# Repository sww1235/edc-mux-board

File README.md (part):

# EDC-MUX-Board

This is part of the [EDC harness
project](https://github.com/sww1235/edc-harness) and provides, audio and PTT
routing and control routing.

This branch uses an FPGA to do digital audio mixing and muxing as well as signal
routing.

Due to using a FPGA, the functionality of the
[mixer](https://github.com/sww1235/portable-line-mixer) is also incorperated.

The initial plan is to use VHDL as the language of choice and then choose a FPGA
based on the actual requirements of the project.

All code, schematics and pcb layouts in this repo are released under MIT, unless
they are licensed under another license, in which case they are under that
license. If you are the maintainer of code that I have used in this project and
consider my license to be incompatible with your license, create an issue and we
can discuss it. This is a personal project with no hope or intention of ever
commercializing it.

## Overview of FPGA logic

All digital audio is using the I2S interface with PCM audio. Need a serial to
parallel converter to take serial data and turn it into parallel data that can
be fed into the parallel multipliers etc.

probably use existing off the shelf i2s to parallel vhdl blocks from
<https://opencore.com> with some modifications. Use 18 bit internal
busses.

Current plan is to use i2s to parallel converter from
[here](https://opencores.org/project/i2s_to_parallel) and modify it for i2s
output.

Use 16 bit audio with 18 bit adders/multipliers.

Digital volume control is done via 18x18 bit multipliers outputing to a double
width bus. IE
`S32 out_PCM = ((S18 ch1_PCM * S18 ch1_gain) + (S18 ch2_PCM * S18 ch2_gain) ... )`
where all S18 are only holding 16 bit signed values but shifted so MSB is at B17 rather than B15.

## Design Notes

Use ATSAMD21J18A microprocessor (ARM Cortex M0+), with separate ethernet mac+phy
chip (probably Wiznet W5500).

Use  TLV320AIC3206 from TI for the headset connections. (Integrated stereo
headphone amplifier along with ADC for mic).

Use MAX4910 4PDT beyond the rail switch to switch between headphone and line out
on the CODEC. Use

Use Master clock with clock buffers to provide MCLK for CODECs, and FPGA.
Additionally, use to clock microprocessor. Might have to use multi output clock
generator to run both wiznet chip and others off one generator.

Best plan is to run all IO at 3.3V LVCMOS standard including clocks.

2x 1:8 LVCMOS fan out clock buffer for 16 CODECs: CDCLVC1108 from TI.

CDCE706 clock generator with 6 independant outputs.

P82B96 bidirectional i2c bus buffer and voltage converter, used for interfacing
to device interface boards.

Use SiTIME MEMS Oscillator SiT1602BI-71-33E-48.000000, connect to RefP input on
clock generator

Use TS12A4514 NO SPST switches for PTT signalling on Interface boards.
Alternatively, if large numbers of switches are needed use a direct i2c
controlled XPST switch rather than using multiple chips.

## SAMD21 IO multiplexed function reference

| Pin | IO Pin | Multiplexed Peripheral function | Connected signal |
|-----|--------|---------------------------------|------------------|
| 10  | PB07   | N/A                             | RESETI2C         |
| 11  | PB08   |          |               |
| 12  | PB09   |          |               |
| 17  | PA08   | SERCOM0/PAD\[0\]                | MOSI             |
| 18  | PA09   | SERCOM0/PAD\[1\]                | \~SS             |
| 19  | PA10   | SERCOM0/PAD\[2\]                | MISO             |
| 20  | PA11   | SERCOM0/PAD\[3\]                | SCK              |
| 23  | PB10   | EXTINT\[10\]                    | CRC_ERROR        |
| 24  | PB11   | EXTINT\[11\]                    | CONF_DONE        |
| 25  | PB12   | SERCOM4/PAD\[0\]  (SDA)         | SDA              |
| 26  | PB13   | SERCOM4/PAD\[1\]  (SCL)         | SCL              |
| 29  | PA12   | EXTINT\[12\]                    | DEV_INT0         |
| 30  | PA13   | EXTINT\[13\]                    | DEV_INT1         |
| 31  | PA14   | XIN (external clock in)         | CLK3_MCU         |
| 32  | PA15   | EXTINT\[15\]                    | DEV_INT2         |
| 35  | PA16   | EXTINT\[0\]                     | DEV_INT3         |
| 36  | PA17   | EXTINT\[1\]                     | DEV_INT4         |
| 37  | PA18   | EXTINT\[2\]                     | DEV_INT5         |
| 38  | PA19   | EXTINT\[3\]                     | DEV_INT6         |
| 41  | PA20   | EXTINT\[4\]                     | DEV_INT7         |
| 42  | PA21   | EXTINT\[5\]                     | ATTACH_INT       |
| 43  | PA22   | EXTINT\[6\]                     | INIT_DONE        |
| 44  | PA23   | EXTINT\[7\]                     | \~STATUS         |
| 45  | PA24   | USB/DM                          | USB_D-           |
| 46  | PA25   | USB/DP                          | USB_D+           |
| 57  | PA30   | SWCLK                           | SWCLK            |
| 58  | PA31   | SWDIO                           | SWDIO            |

Available interrupts on:

Pin 11 / Pin 53 - EXTINT\[8\]
Pin 12 - EXTINT\[9\]
Pin 27 / Pin 59 - EXTINT\[14\]

## Device Interface Notes

Almost all devices are going to have to have an interface board to connect
between the 12 pin connector, and whatever IO is on the actual device.

The original hope was to only have passive components there, but this is looking
to be less practical now, especially since ptt signalling takes up 2 pins, and
is only needed on a very small percentage of devices. Additionally some radios
etc, need multiple ptt switch contacts.

New plan is to have semi-custom **As Small As Possible** interface boards for
devices. These might also simplify providing power to and from the devices
through the power distribution box.

Standardize the interface between mux board and interface. See
**Interface Specs** below for details.

Two different overall types of device: Headset and Device.

The Headset type includes headphones or earbuds that will be connected to the HP
terminals on the TLV320AIC3206. The device type has line outputs. All line
inputs need to be level adjusted with an adjustable pad as seen below. Mics
should be biased as necessary on the interface board and not expect biasing from
the TLV320AIC3206.

In general, each interface board has an I2C IO expander and a I2C flash chip (On
Semi CAT24C16 in WLCSP4 package) containing a board type number, which is read
by the microprocessor in order to set up the appropriate control logic and
determine the appropriate audio levels for the Codec. There will also be a
P82B96 chip for I2C level conversion for "long" distance signalling.

The detection of connection and disconnection of interfaces, is done via an
External Interrupt on the MCU, and with the `ID_PIN` on the connector connected
to ground, so when the device is connected, the pin will flip from high to low,
and when disconnected, it will flip from low to high via an external pull up
resistor on the main board.

There will also be application specific hardware such as ptt signalling or
volume control interpretation for headsets.

### Radio Interface Board Example

ptt switch for each channel, audio passthrough and bias voltage blocking

Has separate power connection

### Smartphone interface

Provides media control of smartphone, audio passthrough and bias voltage blocking.

Media control may be provided via emulating a headset or through some form of USB control.

Note: Android devices use different pinout and resistors to apple devices. Much
more feasible to support Android than Apple.

## Interface specs

Connector pinout:
(directions relative to mux (input = connecting to input on codec))

| Pin | Signal      |
|:----|:------------|
| 1   | SCL_HV      |
| 2   | SDA_HV      |
| 3   | Audio GND   |
| 4   | R Audio OUT |
| 5   | L Audio OUT |
| 6   | L Audio IN  |
| 7   | R Audio IN  |
| 8   | I2C_INT     |
| 9   | ID_PIN      |
| 10  | GND         |
| 11  | GND         |
| 12  | +12V        |

All analog audio IO is done at consumer line level. (IO direction is referenced
to MUX)

Consumer line level uses dBV as its reference. To convert between dBV and
voltage use following formulae:

```math
dBV => 20 * log(Vx/Vref)

0 dBV=Vref=1V

Vx is input voltage (RMS)
```

TLV320AIC3206 will accept signals with max value of 0.5VRMS. Probably need a pad
circuit like below to reduce voltage levels for line inputs. This pad circuit
will be implemented on an external interface board if needed. For general
consumer line level inputs, provide a adjustable resistor to tune VRMS so as to
not overdo attenuation if not needed.

(Device Output) Resistor divider with ~40dB attenuation. Attenuation in dB = 20*
log10((R1 + R2)/R2).

```
Input: o-----^v^v^v--o---o Output
               R1    |
                     >
                 R2  <
                     >
                     >
                     |
                 GND V
```

## I2C commands

Potentially generate interrupt on any physical input change to trigger a read
from i2c master. Will need to set data in `data_to_master` register then set
read_req high. (depends on how fast arduino can respond to interrupt)

Always have master send three bytes. Some instructions will ignore third byte.

### Command Explanations

#### Matrix Mixer:

All outputs receive all inputs. First want to select which output, then select
the volume register associated with that output and the selected input. Then
finally set the actual volume level.

<table>

<tr>

<th>Primary Bit Pattern (Command)</th>
<th>Secondary Bit Pattern (selection/data)</th>
<th>Tertiary bit pattern (data)</th>
<th>Description</th>

</tr>

<tr>

<td> <code>000X.XXXX</code> </td>

<td> <code>000Y.YYYY</code> </td>

<td> <code>VVVV.VVVV</code> </td>

<td> Matrix mixer controls. </br>Channels are represented with i2s channel 0
(left) using even numbers (starting from 0) and i2s channel 1 (right) using odd
numbers, so device 0 channel 0 is <code>00000</code> while device 1 channel 1 is
<code>00011</code>. The inputs and outputs are treated as 32 mono channels each
and left and right are only important in the control software. </br> Primary
selects output with bits 0-4.</br> Secondary selects which input volume is being
controlled with bits 0-4. </br> Tertiary is a 8 bit representation of the linear
volume control of the input in the output. Value from 0 to 255.
</br>So to zero the volume of input 4 channel 1 in output 8 channel 2,
you would send 3 i2c messages: <code>0001.1000</code> => <code>0000.0100</code>
=> <code>0000.0000</code></td>

</tr>

<tr>

<td> <code>01XX.XXXX</code> </td>

<td>  </td>

<td> </td>

<td>Reserved</td>

</tr>

<tr>

<td> <code>10XX.XXXX</code> </td>

<td>  </td>

<td> </td>

<td>Reserved</td>

</tr>

<tr>

<td> <code>1100.000X</code> </td>

<td> </td>

<td> </td>

<td>Reserved</td>

</tr>

</table>

## General Notes

Audio in PCM format is sampled at the sampling rate (normally 44.1kHz(CD) or
48kHz(DVD)) using 16-24 bits of resolution. Meaning each sample is represented
by a 16 to 24 bit number.

Therefor reading i2s data is clock in 16 bits of data into the left register,
then clock in 16 bits of data into the right register and repeat.

I2S by spec represents data in 2s complement format. In any bit width
conversion, truncation or zero fill is applied. Quoting from the I2S spec:

>When the system word length is greater than the transmitter word
>length, the word is truncated (least significant data bits are set to ‘0’)
>for data transmission. If the receiver is sent more bits than its word
>length, the bits after the LSB are ignored. On the other hand, if the
>receiver is sent fewer bits than its word length, the missing bits are
>set to zero internally. And so, the MSB has a fixed position, whereas
>the position of the LSB depends on the word length. The transmitter
>always sends the MSB of the next word one clock period after the
>WS changes.

## Extra parts

-   767KS1(X) 0.084 \[2.1\] id/od sealed locking power plug switchcraft
-   PCL722AS 0.08 \[2.0\] id/od sealed locking power jack switchcraft (these
    sizes are compatible with high amperage version
-   JCAP  power jack cover
-   35FM3AULS - Sealed locking 3.5mm panel mount jack switchcraft
-   35HDLBAU(S) 3.5mm sealed locking plug switchcraft (S=0.175 diameter cable, no S=0.29 diameter cable)

## TODO

-   CODE
-   Case
    -   Change lid screws to M2.5
    -   Move Oring inside screw line (use same as on portable line mixer)
    -   weight reduction on chassis and lid. Shrink wall thickness to 0.125",
        leave ribs on base for stiffness
    -   leave sealing flange and ribs on lid
    -   leave connector sides full thickness

## Power Consumption (Worst Case Assumptions)

| Device (Current Drawn) | +12V | +3V3  | +1V8  | +2V5   | +1V2  |
|:-----------------------|------|-------|-------|--------|-------|
| FPGA                   | 0A   | 20mA  | 0A    | 40mA   | 400mA |
| CODEC x16              | 0A   | 10mA  | 40mA  | 0A     | 0A    |
| P82B96 x16             | 2mA  | 0A    | 0A    | 0A     | 0A    |
| MAX4910 x16            | 0A   | 5uA   | 0A    | 0A     | 0A    |
| TCA9555                | 0A   | 2mA   | 0A    | 0A     | 0A    |
| TCA9548A x2            | 0A   | 35uA  | 0A    | 0A     | 0A    |
| CDCLVC1108 x2          | 0A   | 10mA  | 0A    | 0A     | 0A    |
| W5500                  | 0A   | 132mA | 0A    | 0A     | 0A    |
| SAMD21 MCU             | 0A   | 25mA  | 0A    | 0A     | 0A    |
|                        |      |       |       |        |       |
| Totals                 | 32mA | 360mA | 640mA | 40mA   | 400mA |
| Total @ 3V3 (+20%)     | 0A   | 360mA | 419mA | 36.4mA | 175mA |
| Total @ 12V (+20%)     | 32mA | 327mA | 0A    | 0A     | 0A    |
| Total 12V required     | 360mA | @12V~=4.32W  |
### CODEC Summary

From Application Guide:

Stereo ADC power consumption w/ DVDD == AVDD == 1V8, 48kHz:

Highest Performance Config (max listed) = 18.2mW
Normal (max listed) = 11.5mW

Stereo DAC power consumption w/ DVDD == AVDD == 1V8, 48kHz:

Headphone out (32Ω) (max listed) = 10.9mW

Line out (max listed) = 9.2mW

Worst case assumption of DAC + ADC = 30mA

Assume +10mA for core, +10mA for IO

### SAMD MCU Summary

Static Power draw 4.5mA (worst case)

\+ SERCOM.I2CM 70uA (worst case estimate)

\+ SERCOM.SPI 70uA (worst case estimate)

\+ ADC x16 1.25mA (absolute worst case, since sampling rate is far lower than datasheet numbers)

Total = 24.64mA ~=25mA

## Acknowledgements

I2S to parallel VHDL from
[opencores](https://opencores.org/project/i2s_to_parallel) released under GPL

I2C slave VHDL in submodule from
[here](https://github.com/sww1235/FPGA-I2C-Slave) which was [forked from
here](https://github.com/oetr/FPGA-I2C-Slave) released under MIT.

## References

-   <http://www.epanorama.net/circuits/line_to_mic.html>
-   <http://www.n1gy.com/headset-adaptor.html>
-   <http://www.mobilinkd.com/category/hacking/>
-   <http://ham.stackexchange.com/questions/5244/2-pin-kenwood-to-sound-card-beofeng-uv-82hp-asus-xonar-essence-stx>
-   <http://uuki.kapsi.fi/dl/uv5r_spkmic.pdf>
-   <http://www.n1gy.com/headset-adaptor-for-kenwood--baofeng-and-wouxun-hts.html>
-   <http://electronics.stackexchange.com/questions/71335/how-to-amplify-electret-microphone-to-range-from-0-5v-with-bias-of-2-5v>
-   <https://www.invensense.com/wp-content/uploads/2015/02/Using-a-MEMS-Microphone-in-a-2-Wire-Microphone-Circuit.pdf>
-   <http://www.brenorbrophy.com/HG/head_set_ptt.htm>
-   <http://electronics.stackexchange.com/questions/25229/do-electret-condenser-microphones-require-phantom-power>
-   <http://electronics.stackexchange.com/questions/27452/coupling-electret-microphone-input-to-linear-audio-output?rq=1>
-   <http://electronics.stackexchange.com/questions/261258/electret-microphone-how-does-it-work?rq=1>
-   <https://forums.radioreference.com/radio-direction-finding-forum/297920-baofeng-foxhunt-transmitter.html>
-   <https://www.reddit.com/r/amateurradio/comments/2jd4wr/line_level_to_high_impedance_input/>
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
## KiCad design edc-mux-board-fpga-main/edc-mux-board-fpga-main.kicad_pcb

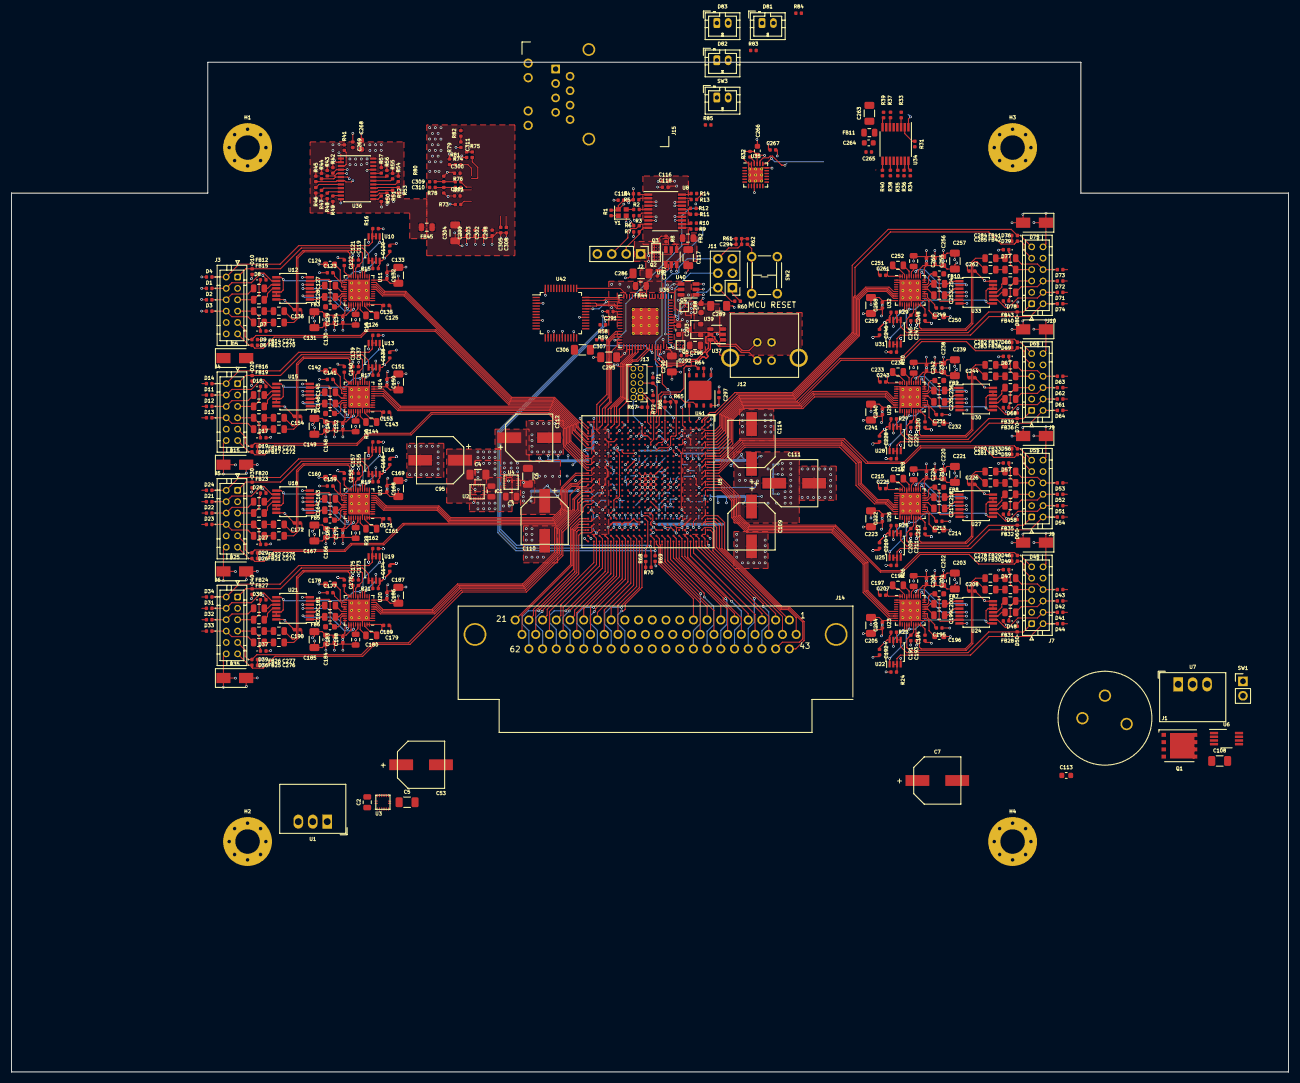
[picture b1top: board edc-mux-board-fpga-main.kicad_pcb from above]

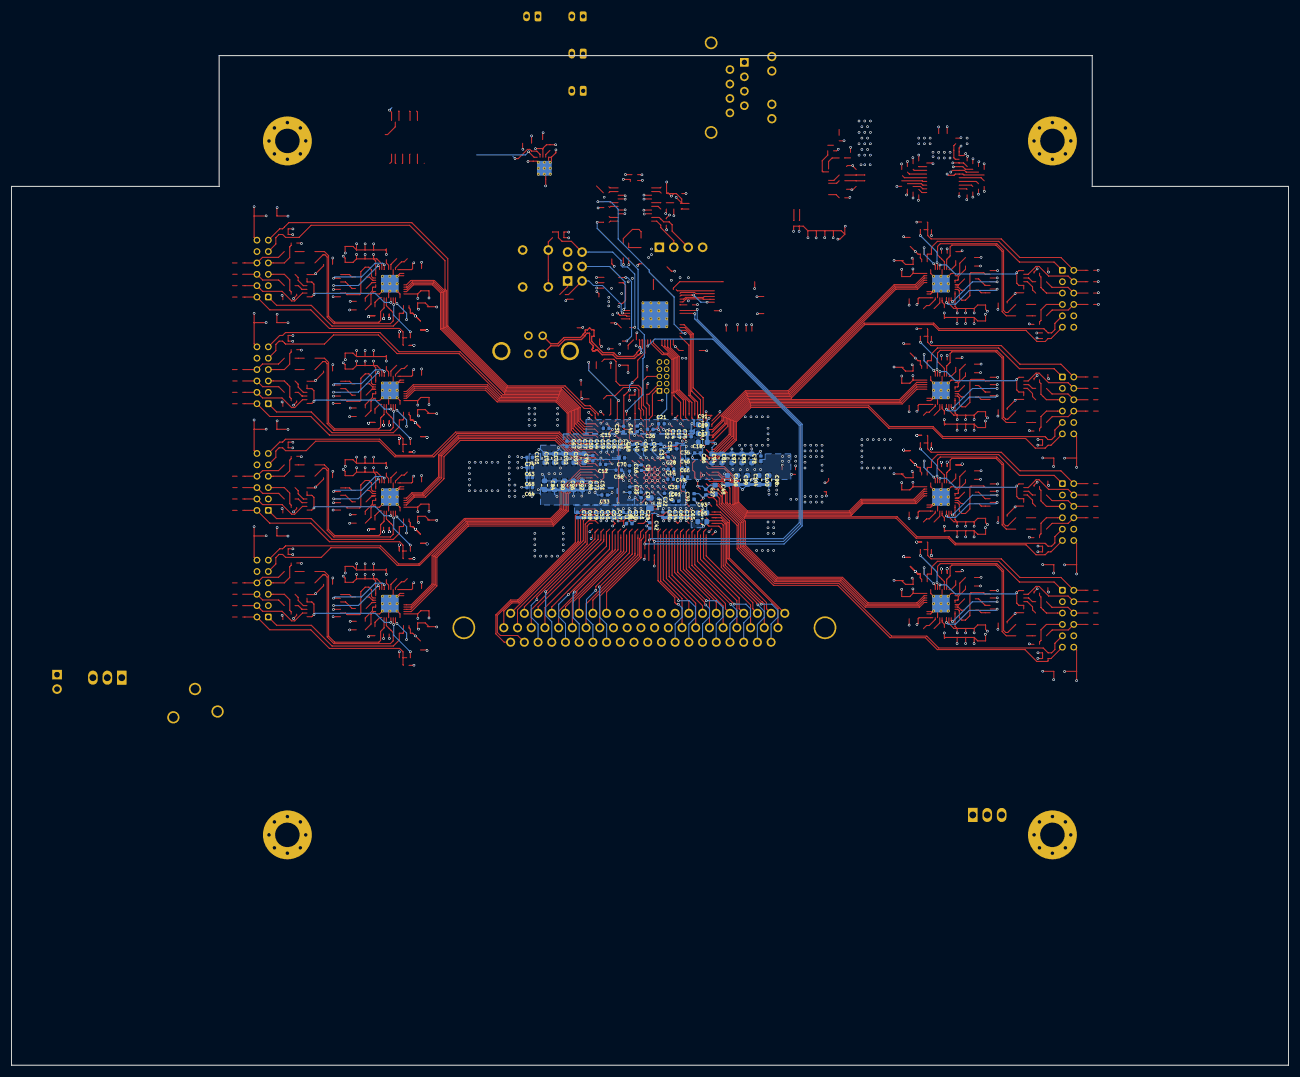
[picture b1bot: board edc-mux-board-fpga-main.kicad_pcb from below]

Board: 4 copper layers, 224.5 x 177.5 mm, 593 parts (99 on the bottom side), 460 nets.

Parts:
C1, C2, C3: 4.7uF X7R; C_0805_2012Metric
C4, C5, C6, C108, C117, C131, C133, C149, C151, C167, C169, C185, C187, C203, C205, C221, C223, C239, C241, C257, C259, C263, C286, C289, C290, C295, C304, C306: 10uF X7R; C_1206_3216Metric
C7, C53, C95, C109, C110, C111, C112, C114: 47uF; CP_ELEC_8.3x8.3x11.7mm_SMD
C8, C9, C10, C11, C12, C13, C14, C15, C16, C17, C18, C19, C20, C21, C22, C23, C24, C25, C26, C28, C29, C31, C32, C34, C37, C305: 4.7nF X7R; C_0402_1005Metric
C27, C30, C33, C36, C39, C41, C44, C47, C50, C52, C55, C57, C59, C60, C62, C308: 10nF X7R; C_0402_1005Metric
C35, C38, C40, C43, C46, C49, C51, C54, C56, C58: 47nF X7R; C_0402_1005Metric
C42, C45, C61, C63, C64, C65, C66, C67, C68, C69, C70, C71, C72, C73, C74, C75, C76, C77, C78, C79, C80, C82, C115, C116, C118, C120, C122, C123, C129, C132, C134, C135, C136, C138, C140, C141, C147, C150, C152, C153, C154, C156, C158, C159, C165, C168, C170, C171, C172, C174, C176, C177, C183, C186, C188, C189, C190, C192, C194, C195, C201, C204, C206, C207, C208, C210, C212, C213, C219, C222, C224, C225, C226, C228, C230, C231, C237, C240, C242, C243, C244, C246, C248, C249, C255, C258, C260, C261, C262, C265, C267, C269, C287, C291, C292, C297, C298, C299, C300, C301, C302, C303, C307: 100nF X7R; C_0402_1005Metric
C48, C85, C87, C89, C91, C93, C98, C99, C100, C101, C102, C103, C104, C105, C106, C107, C124, C130, C142, C148, C160, C166, C178, C184, C196, C202, C214, C220, C232, C238, C250, C256, C264, C266, C268, C288, C293: 1uF X7R; C_0603_1608Metric
C81, C83, C84, C86, C88, C90, C92, C94, C96, C97, C113: 220nF X7R; C_0603_1608Metric
C119, C121, C137, C139, C155, C157, C173, C175, C191, C193, C209, C211, C227, C229, C245, C247: 33pF NP0; C_0402_1005Metric
C125, C126, C143, C144, C161, C162, C179, C180, C197, C198, C215, C216, C233, C234, C251, C252, C296: 2.2uF X7R; C_0805_2012Metric
C127, C128, C145, C146, C163, C164, C181, C182, C199, C200, C217, C218, C235, C236, C253, C254, C270, C271, C272, C273, C274, C275, C276, C277, C278, C279, C280, C281, C282, C283, C284, C285: 1uF X7R flex; C_0805_2012Metric
C294: 100pF C0G; C_0402_1005Metric
C309, C310: 6.8nF X7R; C_0402_1005Metric
C311: 22nF X7R; C_0402_1005Metric
D1, D2, D3, D4, D6, D7, D8, D9, D10, D11, D12, D13, D14, D16, D17, D18, D19, D20, D21, D22, D23, D24, D26, D27, D28, D29, D30, D31, D32, D33, D34, D36, D37, D38, D39, D40, D41, D42, D43, D44, D46, D47, D48, D49, D50, D51, D52, D53, D54, D56, D57, D58, D59, D60, D61, D62, D63, D64, D66, D67, D68, D69, D70, D71, D72, D73, D74, D76, D77, D78, D79, D80: 30pF 30kV; D_0402_1005Metric
D5, D15, D25, D35, D45, D55, D65, D75: 12V_Vrso; D_SMA
D81: LINK_GRN; JST_PH_B2B-PH-K_1x02_P2.00mm_Vertical
D82: ACT_YLW; JST_PH_B2B-PH-K_1x02_P2.00mm_Vertical
D83: PWR_RED; JST_PH_B2B-PH-K_1x02_P2.00mm_Vertical
FB1, FB2, FB11, FB12, FB13, FB14, FB15, FB16, FB17, FB18, FB19, FB20, FB21, FB22, FB23, FB24, FB25, FB26, FB27, FB28, FB29, FB30, FB31, FB32, FB33, FB34, FB35, FB36, FB37, FB38, FB39, FB40, FB41, FB42, FB43, FB44, FB45: 600Ω @ 100MHz; L_0805_2012Metric
FB3, FB4, FB5, FB6, FB7, FB8, FB9, FB10: 220Ω/2A; L_0603_1608Metric
H1, H2, H3, H4: MountingHole_Pad; MountingHole_4.3mm_M4_Pad_Via
J1: Power In; PCL712AS
J2: OSC_PRG_HDR; PinHeader_1x04_P2.54mm_Vertical
J3, J4, J5, J6, J7, J8, J9, J10: Device; JST_PHD_B12B-PHDSS_2x06_P2.00mm_Vertical
J11: PRG/SWD; PinHeader_2x03_P2.54mm_Vertical
J12: USB PRG; UJ2-BV-1-TH
J13: FPGA_JTAG; PinHeader_2x05_P1.27mm_Vertical
J14: DC-62F; 09564525612
J15: RJ45_Magnetics_100BaseTX_No_LEDS; J1_Series_RJ45
Q1: CSD18501Q5A; TDSON-8-1
Q2, Q3, Q4, Q5: CSD22206W; DSBGA9
R1, R3, R4, R5, R60, R67: 1kΩ; R_0402_1005Metric
R2, R74, R75, R76, R77: 0Ω; R_0402_1005Metric
R6, R7, R31, R32, R41, R42, R43, R44, R45, R46, R47, R48, R49, R50, R51, R52, R53, R54, R55, R56, R57, R58, R59, R65, R66, R68, R69, R70, R71, R72: 10kΩ; R_0402_1005Metric
R8: 470kΩ; R_0402_1005Metric
R9, R10, R11, R12, R13, R14, R33, R34, R35, R36, R37, R38, R39, R40: 5Ω; R_0402_1005Metric
R15, R16, R17, R18, R19, R20, R21, R22, R23, R24, R25, R26, R27, R28, R29, R30: 750Ω; R_0402_1005Metric
R61: 2k2Ω; R_0402_1005Metric
R62, R83, R84, R85: 330Ω; R_0402_1005Metric
R64: 25Ω; R_0402_1005Metric
R73: 12.4Ω 1%; R_0402_1005Metric
R78, R80: 82Ω 1%; R_0402_1005Metric
R79, R81: 49.9Ω 1%; R_0402_1005Metric
R82: 10Ω 1%; R_0402_1005Metric
SW1: Power Switch; PinHeader_1x02_P2.54mm_Vertical
SW2: Reset (Microprocessor); TL1105
SW3: LED_EN; JST_PH_B2B-PH-K_1x02_P2.00mm_Vertical
U1: R-78B3.3-2.0; Converter_DCDC_RECOM_R-78B-2.0_THT
U2, U3: EP5358HUI; ENPIRION_QFN16_2.5x2.25x1.1mm-0.4mm
U4: EP5358LUI; ENPIRION_QFN16_2.5x2.25x1.1mm-0.4mm
U5: 10CL040YF484I7G; FBGA-484_23.0x23.0mm_Layout22x22_P1.0mm
U6: LM74610-Q1; VSSOP-8_3.0x3.0mm_P0.65mm
U7: R-78B12-2.0; Converter_DCDC_RECOM_R-78B-2.0_THT
U8: CDCE706; TSSOP-20_4.4x6.5mm_P0.65mm
U9, U40: LTC4412; TSOT-23-6
U10, U13, U16, U19, U22, U25, U28, U31: P82B96; TSSOP-8_3x3mm_P0.65mm
U11, U14, U17, U20, U23, U26, U29, U32: TLV320AIC3206; UQFN-40-1EP_5x5mm_P0.4mm_EP3.8x3.8mm_ThermalVias
U12, U15, U18, U21, U24, U27, U30, U33: FSA2367; TSSOP-14_4.4x5mm_P0.65mm
U34: CDCLVC1108; TSSOP-16_4.4x5mm_P0.65mm
U35: TCA9555RTWR; QFN-24-1EP_4x4mm_P0.5mm_EP2.6x2.6mm_ThermalVias
U36: TCA9548A; TSSOP-24_4.4x7.8mm_P0.65mm
U37: TPD3S014; SOT-23-6
U38: SAMD21JXXAM; QFN-64-1EP_9x9mm_P0.5mm_EP4.7x4.7mm_ThermalVias
U39: MCP1812; SOT-23
U41: S25FL128L; WSON-8-1EP_6x5mm_P1.27mm_EP3.4x4mm
U42: W5500; TQFP-48_7x7mm_P0.5mm
Y1: SiT1602BI-71-33E-48.000000; Crystal_SMD_2016-4Pin_2.0x1.6mm

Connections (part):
+1V2: C6.1, C8.1, C9.1, C10.1, C13.1, C16.1, C19.1, C22.1, C25.1, C28.1, C31.1, C35.1, C38.1, C40.1, C43.1, C46.1, C49.1, C51.1, C54.1, C56.1, C58.1, C61.1, C63.1, C64.1, C66.1, C68.1, C70.1, C72.1, C74.1, C76.1, C78.1, C81.1, C83.1, C84.1, C86.1, C88.1, C90.1, C92.1, C94.1, C96.1, C97.1, C98.1, C99.1, C100.1, C101.1, C102.1, C103.1, C104.1, C105.1, C106.1, C107.1, C109.1, C110.1, C111.1, C112.1, C114.1, FB1.1, U4.5, U4.7, U4.8, U5.G12, U5.H9, U5.J10, U5.J11, U5.J12, U5.J13, U5.J14, U5.J16, U5.K9, U5.K14, U5.K15, U5.L9, U5.L14, U5.L16, U5.M9, U5.M14, U5.M15, U5.N9, U5.N14, U5.P9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
+1V8: C5.1, C129.2, C130.2, C131.2, C134.2, C135.2, C147.2, C148.2, C149.2, C152.2, C153.2, C165.2, C166.2, C167.2, C170.2, C171.2, C183.2, C184.2, C185.2, C188.2, C189.2, C201.2, C202.2, C203.2, C206.2, C207.2, C219.2, C220.2, C221.2, C224.2, C225.2, C237.2, C238.2, C239.2, C242.2, C243.2, C255.2, C256.2, C257.2, C260.2, C261.2, U3.5, U3.7, U3.8, U11.29, U11.30, U11.32, U11.39, U11.40, U14.29, U14.30, U14.32, U14.39, U14.40, U17.29, U17.30, U17.32, U17.39, U17.40, U20.29, U20.30, U20.32, U20.39, U20.40, U23.29, U23.30, U23.32, U23.39, U23.40, U26.29, U26.30, U26.32, U26.39, U26.40, U29.29, U29.30, U29.32, U29.39, U29.40, U32.29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
+2V5: C4.1, C11.1, C14.1, C17.1, C20.1, C23.1, C26.1, C29.1, C32.1, C34.1, C37.1, C41.1, C44.1, C47.1, C50.1, C52.1, C55.1, C57.1, C59.1, C60.1, C62.1, C65.1, C67.1, C69.1, C71.1, C73.1, C75.1, C77.1, C79.1, C80.1, C82.1, C85.1, C87.1, C89.1, C91.1, C93.1, C95.1, J13.9, R71.2, R72.2, U2.5, U2.7, U2.8, U5.F18, U5.G6, U5.T6, U5.U18
+3V3: C1.1, C2.1, C3.1, C7.1, C12.1, C15.1, C18.1, C21.1, C24.1, C27.1, C30.1, C33.1, C36.1, C39.1, C42.1, C45.1, C48.1, C53.1, C132.2, C133.1, C136.2, C150.2, C151.1, C154.2, C168.2, C169.1, C172.2, C186.2, C187.1, C190.2, C204.2, C205.1, C208.2, C222.2, C223.1, C226.2, C240.2, C241.1, C244.2, C258.2, C259.1, C262.2, C263.1, C266.1, C267.2, C268.1, C269.2, C294.2, C297.2, C306.2, C307.2, FB11.2, FB45.2, J11.1, J13.8, Q2.C1, Q2.C2, Q2.C3, Q4.C1, Q4.C2, Q4.C3, R32.2, R41.2, R42.2, R43.2, R44.2, R45.2, R46.2, R47.2, R48.2, R49.2, R50.2, R51.2, R52.2, R53.2, R54.2, R55.2, R56.2, R57.2, R58.2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
+12V: C120.1, C138.1, C156.1, C174.1, C192.1, C210.1, C228.1, C246.1, D5.1, D15.1, D25.1, D35.1, D45.1, D55.1, D65.1, D75.1, J3.12, J4.12, J5.12, J6.12, J7.12, J8.12, J9.12, J10.12, J14.9, J14.12, J14.13, J14.30, J14.31, J14.34, R15.1, R16.1, R17.1, R18.1, R19.1, R20.1, R21.1, R22.1, R23.1, R24.1, R25.1, R26.1, R27.1, R28.1, R29.1, R30.1, U1.1, U7.3, U10.8, U13.8, U16.8, U19.8, U22.8, U25.8, U28.8, U31.8
/ATTACH_INT: U5.R1, U38.42
/Bottom Side Connector Interconnects/BCLK8: J14.15, U5.R22
/Bottom Side Connector Interconnects/BCLK9: J14.17, U5.V22
/Bottom Side Connector Interconnects/BCLK10: J14.19, U5.AA22
/Bottom Side Connector Interconnects/BCLK11: J14.21, U5.AB18
/Bottom Side Connector Interconnects/BCLK12: J14.2, U5.A20
/Bottom Side Connector Interconnects/BCLK13: J14.4, U5.D22
/Bottom Side Connector Interconnects/BCLK14: J14.6, U5.G22
/Bottom Side Connector Interconnects/BCLK15: J14.8, U5.K22
/Bottom Side Connector Interconnects/DIN8: J14.14, U5.P22
/Bottom Side Connector Interconnects/DIN9: J14.16, U5.U22
/Bottom Side Connector Interconnects/DIN10: J14.18, U5.Y22
/Bottom Side Connector Interconnects/DIN11: J14.20, U5.AB19
/Bottom Side Connector Interconnects/DIN12: J14.1, U5.A19
/Bottom Side Connector Interconnects/DIN13: J14.3, U5.C22
/Bottom Side Connector Interconnects/DIN14: J14.5, U5.F22
/Bottom Side Connector Interconnects/DIN15: J14.7, U5.J22
/Bottom Side Connector Interconnects/DOUT8: J14.35, U5.P21
/Bottom Side Connector Interconnects/DOUT9: J14.37, U5.U21
/Bottom Side Connector Interconnects/DOUT10: J14.39, U5.Y21
/Bottom Side Connector Interconnects/DOUT11: J14.41, U5.AA19
/Bottom Side Connector Interconnects/DOUT12: J14.22, U5.B19
/Bottom Side Connector Interconnects/DOUT13: J14.24, U5.C21
/Bottom Side Connector Interconnects/DOUT14: J14.26, U5.F21
/Bottom Side Connector Interconnects/DOUT15: J14.28, U5.J21
/Bottom Side Connector Interconnects/WCLK8: J14.36, U5.R21
/Bottom Side Connector Interconnects/WCLK9: J14.38, U5.V21
/Bottom Side Connector Interconnects/WCLK10: J14.40, U5.AA21
/Bottom Side Connector Interconnects/WCLK11: J14.42, U5.AA18
/Bottom Side Connector Interconnects/WCLK12: J14.23, U5.B20
/Bottom Side Connector Interconnects/WCLK13: J14.25, U5.D21
/Bottom Side Connector Interconnects/WCLK14: J14.27, U5.G21
/Bottom Side Connector Interconnects/WCLK15: J14.29, U5.K21
/Bottom Side Connector Interconnects/~RESET~I2C: J14.33, R41.1, U36.3, U38.10
/CODEC interconnection sheet/BCLK0: U5.AA4, U11.6
/CODEC interconnection sheet/BCLK1: U5.AA8, U14.6
/CODEC interconnection sheet/BCLK2: U5.AA11, U17.6
/CODEC interconnection sheet/BCLK3: U5.AA14, U20.6
/CODEC interconnection sheet/BCLK4: U5.B12, U23.6
/CODEC interconnection sheet/BCLK5: U5.B9, U26.6
/CODEC interconnection sheet/BCLK6: U5.B6, U29.6
/CODEC interconnection sheet/BCLK7: U5.B3, U32.6
/CODEC interconnection sheet/Clock and I2C distribution/CLK_DISTRO_3V3_1: C264.2, C265.1, FB11.1, R31.2, U34.5, U34.10, U34.14
/CODEC interconnection sheet/DIN0: U5.AA3, U11.8
/CODEC interconnection sheet/DIN1: U5.AA7, U14.8
/CODEC interconnection sheet/DIN2: U5.AA10, U17.8
/CODEC interconnection sheet/DIN3: U5.AA13, U20.8
/CODEC interconnection sheet/DIN4: U5.B13, U23.8
/CODEC interconnection sheet/DIN5: U5.B10, U26.8
/CODEC interconnection sheet/DIN6: U5.B7, U29.8
/CODEC interconnection sheet/DIN7: U5.B4, U32.8
/CODEC interconnection sheet/DOUT0: U5.AB3, U11.9
/CODEC interconnection sheet/DOUT1: U5.AB7, U14.9
/CODEC interconnection sheet/DOUT2: U5.AB10, U17.9
/CODEC interconnection sheet/DOUT3: U5.AB13, U20.9
/CODEC interconnection sheet/DOUT4: U5.A13, U23.9
/CODEC interconnection sheet/DOUT5: U5.A10, U26.9
/CODEC interconnection sheet/DOUT6: U5.A7, U29.9
/CODEC interconnection sheet/DOUT7: U5.A4, U32.9
/CODEC interconnection sheet/Interface - Connector 0/AUD_GND: D1.1, J3.4, U12.9
/CODEC interconnection sheet/Interface - Connector 0/GND_SENSE: FB3.1, U11.28, U12.6
/CODEC interconnection sheet/Interface - Connector 0/HPL: U11.31, U12.4
/CODEC interconnection sheet/Interface - Connector 0/HPR: U11.33, U12.2
/CODEC interconnection sheet/Interface - Connector 0/HP_~LINE~_SEL: U11.15, U12.8, U12.12, U12.13
/CODEC interconnection sheet/Interface - Connector 0/LINE_OUT_L: C127.1, U12.3
/CODEC interconnection sheet/Interface - Connector 0/LINE_OUT_R: C128.1, U12.1
/CODEC interconnection sheet/Interface - Connector 0/L_IN: C119.2, C271.1, U11.17
/CODEC interconnection sheet/Interface - Connector 0/L_OUT: FB12.2, U12.10
/CODEC interconnection sheet/Interface - Connector 0/REF: C124.2, U11.22
/CODEC interconnection sheet/Interface - Connector 0/R_IN: C121.2, C270.2, U11.18
/CODEC interconnection sheet/Interface - Connector 0/R_OUT: FB15.1, U12.11
/CODEC interconnection sheet/Interface - Connector 0/SCL_HV: D10.1, J3.1, R15.2, U10.5, U10.6
/CODEC interconnection sheet/Interface - Connector 0/SDA_HV: D4.1, J3.2, R16.2, U10.2, U10.3
/CODEC interconnection sheet/Interface - Connector 0/VNEG: C126.2, U11.35
/CODEC interconnection sheet/Interface - Connector 1/AUD_GND: D11.1, J4.4, U15.9
/CODEC interconnection sheet/Interface - Connector 1/GND_SENSE: FB4.1, U14.28, U15.6
/CODEC interconnection sheet/Interface - Connector 1/HPL: U14.31, U15.4
/CODEC interconnection sheet/Interface - Connector 1/HPR: U14.33, U15.2
/CODEC interconnection sheet/Interface - Connector 1/HP_~LINE~_SEL: U14.15, U15.8, U15.12, U15.13
/CODEC interconnection sheet/Interface - Connector 1/LINE_OUT_L: C145.1, U15.3
/CODEC interconnection sheet/Interface - Connector 1/LINE_OUT_R: C146.1, U15.1
/CODEC interconnection sheet/Interface - Connector 1/L_IN: C137.2, C273.1, U14.17
/CODEC interconnection sheet/Interface - Connector 1/L_OUT: FB16.2, U15.10
/CODEC interconnection sheet/Interface - Connector 1/REF: C142.2, U14.22
/CODEC interconnection sheet/Interface - Connector 1/R_IN: C139.2, C272.2, U14.18
/CODEC interconnection sheet/Interface - Connector 1/R_OUT: FB19.1, U15.11
/CODEC interconnection sheet/Interface - Connector 1/SCL_HV: D20.1, J4.1, R17.2, U13.5, U13.6
/CODEC interconnection sheet/Interface - Connector 1/SDA_HV: D14.1, J4.2, R18.2, U13.2, U13.3
/CODEC interconnection sheet/Interface - Connector 1/VNEG: C144.2, U14.35
/CODEC interconnection sheet/Interface - Connector 2/AUD_GND: D21.1, J5.4, U18.9
/CODEC interconnection sheet/Interface - Connector 2/GND_SENSE: FB5.1, U17.28, U18.6
/CODEC interconnection sheet/Interface - Connector 2/HPL: U17.31, U18.4
/CODEC interconnection sheet/Interface - Connector 2/HPR: U17.33, U18.2
/CODEC interconnection sheet/Interface - Connector 2/HP_~LINE~_SEL: U17.15, U18.8, U18.12, U18.13
/CODEC interconnection sheet/Interface - Connector 2/LINE_OUT_L: C163.1, U18.3
/CODEC interconnection sheet/Interface - Connector 2/LINE_OUT_R: C164.1, U18.1
/CODEC interconnection sheet/Interface - Connector 2/L_IN: C155.2, C275.1, U17.17
/CODEC interconnection sheet/Interface - Connector 2/L_OUT: FB20.2, U18.10
/CODEC interconnection sheet/Interface - Connector 2/REF: C160.2, U17.22
/CODEC interconnection sheet/Interface - Connector 2/R_IN: C157.2, C274.2, U17.18
/CODEC interconnection sheet/Interface - Connector 2/R_OUT: FB23.1, U18.11
/CODEC interconnection sheet/Interface - Connector 2/SCL_HV: D30.1, J5.1, R19.2, U16.5, U16.6
/CODEC interconnection sheet/Interface - Connector 2/SDA_HV: D24.1, J5.2, R20.2, U16.2, U16.3
/CODEC interconnection sheet/Interface - Connector 2/VNEG: C162.2, U17.35
/CODEC interconnection sheet/Interface - Connector 3/AUD_GND: D31.1, J6.4, U21.9
/CODEC interconnection sheet/Interface - Connector 3/GND_SENSE: FB6.1, U20.28, U21.6
/CODEC interconnection sheet/Interface - Connector 3/HPL: U20.31, U21.4
/CODEC interconnection sheet/Interface - Connector 3/HPR: U20.33, U21.2
/CODEC interconnection sheet/Interface - Connector 3/HP_~LINE~_SEL: U20.15, U21.8, U21.12, U21.13
/CODEC interconnection sheet/Interface - Connector 3/LINE_OUT_L: C181.1, U21.3
/CODEC interconnection sheet/Interface - Connector 3/LINE_OUT_R: C182.1, U21.1
/CODEC interconnection sheet/Interface - Connector 3/L_IN: C173.2, C277.1, U20.17
/CODEC interconnection sheet/Interface - Connector 3/L_OUT: FB24.2, U21.10
/CODEC interconnection sheet/Interface - Connector 3/REF: C178.2, U20.22
/CODEC interconnection sheet/Interface - Connector 3/R_IN: C175.2, C276.2, U20.18
/CODEC interconnection sheet/Interface - Connector 3/R_OUT: FB27.1, U21.11
/CODEC interconnection sheet/Interface - Connector 3/SCL_HV: D40.1, J6.1, R21.2, U19.5, U19.6
/CODEC interconnection sheet/Interface - Connector 3/SDA_HV: D34.1, J6.2, R22.2, U19.2, U19.3
/CODEC interconnection sheet/Interface - Connector 3/VNEG: C180.2, U20.35
/CODEC interconnection sheet/Interface - Connector 4/AUD_GND: D41.1, J7.4, U24.9
/CODEC interconnection sheet/Interface - Connector 4/GND_SENSE: FB7.1, U23.28, U24.6
/CODEC interconnection sheet/Interface - Connector 4/HPL: U23.31, U24.4
/CODEC interconnection sheet/Interface - Connector 4/HPR: U23.33, U24.2
/CODEC interconnection sheet/Interface - Connector 4/HP_~LINE~_SEL: U23.15, U24.8, U24.12, U24.13
/CODEC interconnection sheet/Interface - Connector 4/LINE_OUT_L: C199.1, U24.3
/CODEC interconnection sheet/Interface - Connector 4/LINE_OUT_R: C200.1, U24.1
/CODEC interconnection sheet/Interface - Connector 4/L_IN: C191.2, C279.1, U23.17
/CODEC interconnection sheet/Interface - Connector 4/L_OUT: FB28.2, U24.10
/CODEC interconnection sheet/Interface - Connector 4/REF: C196.2, U23.22
/CODEC interconnection sheet/Interface - Connector 4/R_IN: C193.2, C278.2, U23.18
/CODEC interconnection sheet/Interface - Connector 4/R_OUT: FB31.1, U24.11
/CODEC interconnection sheet/Interface - Connector 4/SCL_HV: D50.1, J7.1, R23.2, U22.5, U22.6
/CODEC interconnection sheet/Interface - Connector 4/SDA_HV: D44.1, J7.2, R24.2, U22.2, U22.3
/CODEC interconnection sheet/Interface - Connector 4/VNEG: C198.2, U23.35
/CODEC interconnection sheet/Interface - Connector 5/AUD_GND: D51.1, J8.4, U27.9
/CODEC interconnection sheet/Interface - Connector 5/GND_SENSE: FB8.1, U26.28, U27.6
/CODEC interconnection sheet/Interface - Connector 5/HPL: U26.31, U27.4
/CODEC interconnection sheet/Interface - Connector 5/HPR: U26.33, U27.2
/CODEC interconnection sheet/Interface - Connector 5/HP_~LINE~_SEL: U26.15, U27.8, U27.12, U27.13
/CODEC interconnection sheet/Interface - Connector 5/LINE_OUT_L: C217.1, U27.3
/CODEC interconnection sheet/Interface - Connector 5/LINE_OUT_R: C218.1, U27.1
/CODEC interconnection sheet/Interface - Connector 5/L_IN: C209.2, C281.1, U26.17
/CODEC interconnection sheet/Interface - Connector 5/L_OUT: FB32.2, U27.10
/CODEC interconnection sheet/Interface - Connector 5/REF: C214.2, U26.22
/CODEC interconnection sheet/Interface - Connector 5/R_IN: C211.2, C280.2, U26.18
/CODEC interconnection sheet/Interface - Connector 5/R_OUT: FB35.1, U27.11
/CODEC interconnection sheet/Interface - Connector 5/SCL_HV: D60.1, J8.1, R25.2, U25.5, U25.6
/CODEC interconnection sheet/Interface - Connector 5/SDA_HV: D54.1, J8.2, R26.2, U25.2, U25.3
/CODEC interconnection sheet/Interface - Connector 5/VNEG: C216.2, U26.35
/CODEC interconnection sheet/Interface - Connector 6/AUD_GND: D61.1, J9.4, U30.9
/CODEC interconnection sheet/Interface - Connector 6/GND_SENSE: FB9.1, U29.28, U30.6
/CODEC interconnection sheet/Interface - Connector 6/HPL: U29.31, U30.4
/CODEC interconnection sheet/Interface - Connector 6/HPR: U29.33, U30.2
/CODEC interconnection sheet/Interface - Connector 6/HP_~LINE~_SEL: U29.15, U30.8, U30.12, U30.13
/CODEC interconnection sheet/Interface - Connector 6/LINE_OUT_L: C235.1, U30.3
/CODEC interconnection sheet/Interface - Connector 6/LINE_OUT_R: C236.1, U30.1
/CODEC interconnection sheet/Interface - Connector 6/L_IN: C227.2, C283.1, U29.17
/CODEC interconnection sheet/Interface - Connector 6/L_OUT: FB36.2, U30.10
/CODEC interconnection sheet/Interface - Connector 6/REF: C232.2, U29.22
/CODEC interconnection sheet/Interface - Connector 6/R_IN: C229.2, C282.2, U29.18
/CODEC interconnection sheet/Interface - Connector 6/R_OUT: FB39.1, U30.11
/CODEC interconnection sheet/Interface - Connector 6/SCL_HV: D70.1, J9.1, R27.2, U28.5, U28.6
/CODEC interconnection sheet/Interface - Connector 6/SDA_HV: D64.1, J9.2, R28.2, U28.2, U28.3
/CODEC interconnection sheet/Interface - Connector 6/VNEG: C234.2, U29.35
/CODEC interconnection sheet/Interface - Connector 7/AUD_GND: D71.1, J10.4, U33.9
/CODEC interconnection sheet/Interface - Connector 7/GND_SENSE: FB10.1, U32.28, U33.6
/CODEC interconnection sheet/Interface - Connector 7/HPL: U32.31, U33.4
/CODEC interconnection sheet/Interface - Connector 7/HPR: U32.33, U33.2
/CODEC interconnection sheet/Interface - Connector 7/HP_~LINE~_SEL: U32.15, U33.8, U33.12, U33.13
/CODEC interconnection sheet/Interface - Connector 7/LINE_OUT_L: C253.1, U33.3
/CODEC interconnection sheet/Interface - Connector 7/LINE_OUT_R: C254.1, U33.1
/CODEC interconnection sheet/Interface - Connector 7/L_IN: C245.2, C285.1, U32.17
/CODEC interconnection sheet/Interface - Connector 7/L_OUT: FB40.2, U33.10
/CODEC interconnection sheet/Interface - Connector 7/REF: C250.2, U32.22
/CODEC interconnection sheet/Interface - Connector 7/R_IN: C247.2, C284.2, U32.18
/CODEC interconnection sheet/Interface - Connector 7/R_OUT: FB43.1, U33.11
/CODEC interconnection sheet/Interface - Connector 7/SCL_HV: D80.1, J10.1, R29.2, U31.5, U31.6
/CODEC interconnection sheet/Interface - Connector 7/SDA_HV: D74.1, J10.2, R30.2, U31.2, U31.3
/CODEC interconnection sheet/Interface - Connector 7/VNEG: C252.2, U32.35
/CODEC interconnection sheet/MCLK0: R33.1, U11.5
/CODEC interconnection sheet/MCLK1: R37.1, U14.5
/CODEC interconnection sheet/MCLK2: R39.1, U17.5
/CODEC interconnection sheet/MCLK3: R40.1, U20.5
/CODEC interconnection sheet/MCLK4: R38.1, U23.5
/CODEC interconnection sheet/MCLK5: R35.1, U26.5
/CODEC interconnection sheet/MCLK6: R36.1, U29.5
/CODEC interconnection sheet/MCLK7: R34.1, U32.5
/CODEC interconnection sheet/SCL0: R43.1, U10.7, U11.13, U36.5
/CODEC interconnection sheet/SCL1: R45.1, U13.7, U14.13, U36.7
/CODEC interconnection sheet/SCL2: R47.1, U16.7, U17.13, U36.9
/CODEC interconnection sheet/SCL3: R49.1, U19.7, U20.13, U36.11
/CODEC interconnection sheet/SCL4: R51.1, U22.7, U23.13, U36.14
/CODEC interconnection sheet/SCL5: R53.1, U25.7, U26.13, U36.16
/CODEC interconnection sheet/SCL6: R55.1, U28.7, U29.13, U36.18
/CODEC interconnection sheet/SCL7: R57.1, U31.7, U32.13, U36.20
/CODEC interconnection sheet/SDA0: R42.1, U10.1, U11.14, U36.4
/CODEC interconnection sheet/SDA1: R44.1, U13.1, U14.14, U36.6
/CODEC interconnection sheet/SDA2: R46.1, U16.1, U17.14, U36.8
/CODEC interconnection sheet/SDA3: R48.1, U19.1, U20.14, U36.10
/CODEC interconnection sheet/SDA4: R50.1, U22.1, U23.14, U36.13
/CODEC interconnection sheet/SDA5: R52.1, U25.1, U26.14, U36.15
/CODEC interconnection sheet/SDA6: R54.1, U28.1, U29.14, U36.17
/CODEC interconnection sheet/SDA7: R56.1, U31.1, U32.14, U36.19
/CODEC interconnection sheet/WCLK0: U5.AB4, U11.7
/CODEC interconnection sheet/WCLK1: U5.AB8, U14.7
/CODEC interconnection sheet/WCLK2: U5.AB11, U17.7
/CODEC interconnection sheet/WCLK3: U5.AB14, U20.7
/CODEC interconnection sheet/WCLK4: U5.A12, U23.7
/CODEC interconnection sheet/WCLK5: U5.A9, U26.7
/CODEC interconnection sheet/WCLK6: U5.A6, U29.7
/CODEC interconnection sheet/WCLK7: U5.A3, U32.7
/CODEC interconnection sheet/~RESET~0: U11.3, U35.1
/CODEC interconnection sheet/~RESET~1: U14.3, U35.2
/CODEC interconnection sheet/~RESET~2: U17.3, U35.3
/CODEC interconnection sheet/~RESET~3: U20.3, U35.4
/CODEC interconnection sheet/~RESET~4: U23.3, U35.5
/CODEC interconnection sheet/~RESET~5: U26.3, U35.6
/CODEC interconnection sheet/~RESET~6: U29.3, U35.7
/CODEC interconnection sheet/~RESET~7: U32.3, U35.8
/CONF_DONE: R68.1, U5.M18, U38.24
/CRC_ERROR: R69.1, U5.L21, U38.23
/Clocking/3V3_PROT: C117.1, FB2.1, Q2.A2, Q2.A3, Q2.B1, Q2.B2, Q2.B3, Q3.A2, Q3.A3, Q3.B1, Q3.B2, Q3.B3, R8.2, U9.6
/Clocking/+3V3C: C115.2, C116.2, C118.2, FB2.2, R1.1, R4.2, R5.1, R6.1, R7.1, U8.3, U8.7, U8.14, U8.18, Y1.4
/Clocking/+3V3EXT: J2.1, Q3.C1, Q3.C2, Q3.C3
/Clocking/CLK_IN0: R2.1, U8.5
/Clocking/S0: R4.1, U8.1
/Clocking/S1: R5.2, U8.2
/Clocking/SCL: J2.2, R7.2, U8.10
/Clocking/SDA: J2.3, R6.2, U8.9
/Ethernet Connections/+3V3A: C298.2, C299.2, C300.2, C301.2, C302.2, C303.2, C304.2, FB45.1, R79.2, R81.2, R82.2, U42.4, U42.8, U42.11, U42.15, U42.17, U42.21
/Ethernet Connections/ACTLED: R84.2, U42.27
/Ethernet Connections/LED_PWR: D81.2, D82.2, D83.2, SW3.1
/Ethernet Connections/LINKLED: R83.2, U42.25
/Ethernet Connections/MISO: U38.19, U42.34
/Ethernet Connections/MOSI: U38.17, U42.35
/Ethernet Connections/~INT: U38.16, U42.36
/Ethernet Connections/~RESET~_ETH: U38.15, U42.37
/Ethernet Connections/~SS: U38.18, U42.32
/FPGA Interconnects/DEV_ATT0: D6.1, J3.11, U5.AA5
/FPGA Interconnects/DEV_ATT1: D16.1, J4.11, U5.AA9
/FPGA Interconnects/DEV_ATT2: D26.1, J5.11, U5.AA12
/FPGA Interconnects/DEV_ATT3: D36.1, J6.11, U5.AA15
/FPGA Interconnects/DEV_ATT4: D46.1, J7.11, U5.B11
/FPGA Interconnects/DEV_ATT5: D56.1, J8.11, U5.B8
/FPGA Interconnects/DEV_ATT6: D66.1, J9.11, U5.B5
/FPGA Interconnects/DEV_ATT7: D76.1, J10.11, U5.B1
/FPGA Interconnects/DEV_ATT8: J14.56, U5.N22
/FPGA Interconnects/DEV_ATT9: J14.58, U5.T22
/FPGA Interconnects/DEV_ATT10: J14.60, U5.W22
/FPGA Interconnects/DEV_ATT11: J14.62, U5.AB20
/FPGA Interconnects/DEV_ATT12: J14.44, U5.A18
/FPGA Interconnects/DEV_ATT13: J14.46, U5.B22
/FPGA Interconnects/DEV_ATT14: J14.48, U5.E22
/FPGA Interconnects/DEV_ATT15: J14.50, U5.H22
/FPGA Interconnects/DEV_INT0: D9.1, J3.9, U5.AB5
/FPGA Interconnects/DEV_INT1: D19.1, J4.9, U5.AB9
/FPGA Interconnects/DEV_INT2: D29.1, J5.9, U5.AB12
/FPGA Interconnects/DEV_INT3: D39.1, J6.9, U5.AB15
/FPGA Interconnects/DEV_INT4: D49.1, J7.9, U5.A11
/FPGA Interconnects/DEV_INT5: D59.1, J8.9, U5.A8
/FPGA Interconnects/DEV_INT6: D69.1, J9.9, U5.A5
/FPGA Interconnects/DEV_INT7: D79.1, J10.9, U5.B2
/FPGA Interconnects/DEV_INT8: J14.55, U5.N21
/FPGA Interconnects/DEV_INT9: J14.57, U5.T21
/FPGA Interconnects/DEV_INT10: J14.59, U5.W21
/FPGA Interconnects/DEV_INT11: J14.61, U5.AA20
/FPGA Interconnects/DEV_INT12: J14.43, U5.B18
/FPGA Interconnects/DEV_INT13: J14.45, U5.B21
/FPGA Interconnects/DEV_INT14: J14.47, U5.E21
/FPGA Interconnects/DEV_INT15: J14.49, U5.H21
/FPGA Interconnects/MISO: R64.1, U5.K1
/FPGA Interconnects/MOSI: U5.D1, U41.5
/FPGA Interconnects/SCK: U5.K2, U41.6
/FPGA Interconnects/TCK: J13.1, R67.2, U5.L2
/FPGA Interconnects/TDI: J13.5, R71.1, U5.L5
/FPGA Interconnects/TDO: J13.2, U5.L4
/FPGA Interconnects/TMS: J13.3, R72.1, U5.L1
/FPGA Interconnects/~CONFIG: R66.1, U5.K5
/FPGA Interconnects/~CS: U5.E2, U41.1
/INIT_DONE: R70.1, U5.L22, U38.43
/Microprocessor and Support/+3V3USB: C296.2, Q5.C1, Q5.C2, Q5.C3, U39.1
/Microprocessor and Support/+5VUSB: C288.2, C289.2, U37.4, U39.2
/Microprocessor and Support/+5Vin: J12.1, U37.1, U37.3
/Microprocessor and Support/DEV_INT0: U5.Y1, U38.29
/Microprocessor and Support/DEV_INT1: U5.Y2, U38.30
/Microprocessor and Support/DEV_INT2: U5.W1, U38.32
/Microprocessor and Support/DEV_INT3: U5.W2, U38.35
/Microprocessor and Support/DEV_INT4: U5.V1, U38.36
/Microprocessor and Support/DEV_INT5: U5.V2, U38.37
/Microprocessor and Support/DEV_INT6: U5.U1, U38.38
/Microprocessor and Support/DEV_INT7: U5.U2, U38.41
/Microprocessor and Support/MCU_VDDA: C286.2, C287.2, FB44.1, U38.8
/Microprocessor and Support/MCU_VDDCORE: C293.1, U38.55
/Microprocessor and Support/MCU_VDDIO: C290.1, C291.1, C292.1, C295.1, FB44.2, Q4.A2, Q4.A3, Q4.B1, Q4.B2, Q4.B3, Q5.A2, Q5.A3, Q5.B1, Q5.B2, Q5.B3, U38.21, U38.34, U38.48, U38.56, U40.6
/Microprocessor and Support/SCK: U38.20, U42.33
/Microprocessor and Support/SWCLK: J11.2, R60.1, U38.57
/Microprocessor and Support/SWDIO: J11.4, U38.58
/Microprocessor and Support/USB_D+: J12.3, U37.6, U38.46
/Microprocessor and Support/USB_D-: J12.2, U37.5, U38.45
/Microprocessor and Support/~RESET: C294.1, J11.6, R61.1, R62.2, U38.52
/Power Supplies/SW_PWR_IN: C108.1, Q1.1, Q1.2, Q1.3, SW1.2, U6.4
/Power Supplies/VCCDPLL: FB1.2, U5.E17, U5.F6, U5.U6, U5.V17
/SCL: J14.32, R59.1, U5.M1, U35.19, U36.22, U38.26
/SDA: J14.11, R58.1, U5.N1, U35.20, U36.23, U38.25
/~RESET~_FPGA: U5.Y3, U38.28
/~STATUS: R65.1, U5.K6, U38.44
CLK0_FPGA: R9.1, U5.G1
CLK1_CODEC: R10.1, U34.1
CLK2_CODEC: J14.10, R11.1
CLK3_MCU: R12.1, U38.31
CLK4_ETH: R13.1, U42.30
GND: C1.2, C2.2, C3.2, C4.2, C5.2, C6.2, C7.2, C8.2, C9.2, C10.2, C11.2, C12.2, C13.2, C14.2, C15.2, C16.2, C17.2, C18.2, C19.2, C20.2, C21.2, C22.2, C23.2, C24.2, C25.2, C26.2, C27.2, C28.2, C29.2, C30.2, C31.2, C32.2, C33.2, C34.2, C35.2, C36.2, C37.2, C38.2, C39.2, C40.2, C41.2, C42.2, C43.2, C44.2, C45.2, C46.2, C47.2, C48.2, C49.2, C50.2, C51.2, C52.2, C53.2, C54.2, C55.2, C56.2, C57.2, C58.2, C59.2, C60.2, C61.2, C62.2, C63.2, C64.2, C65.2, C66.2, C67.2, C68.2, C69.2, C70.2, C71.2, C72.2, C73.2, C74.2, C75.2, C76.2, C77.2, C78.2, C79.2, C80.2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
unnamed: C113.1, U6.1
unnamed: C113.2, U6.7
unnamed: C122.2, U11.19, U11.20
unnamed: C123.2, U11.24, U11.25
unnamed: C125.1, U11.36
unnamed: C125.2, U11.38
unnamed: C127.2, U11.26
unnamed: C128.2, U11.27
unnamed: C140.2, U14.19, U14.20
unnamed: C141.2, U14.24, U14.25
unnamed: C143.1, U14.36
unnamed: C143.2, U14.38
unnamed: C145.2, U14.26
unnamed: C146.2, U14.27
unnamed: C158.2, U17.19, U17.20
unnamed: C159.2, U17.24, U17.25
unnamed: C161.1, U17.36
unnamed: C161.2, U17.38
unnamed: C163.2, U17.26
unnamed: C164.2, U17.27
unnamed: C176.2, U20.19, U20.20
unnamed: C177.2, U20.24, U20.25
unnamed: C179.1, U20.36
unnamed: C179.2, U20.38
unnamed: C181.2, U20.26
unnamed: C182.2, U20.27
unnamed: C194.2, U23.19, U23.20
unnamed: C195.2, U23.24, U23.25
unnamed: C197.1, U23.36
unnamed: C197.2, U23.38
unnamed: C199.2, U23.26
unnamed: C200.2, U23.27
unnamed: C212.2, U26.19, U26.20
unnamed: C213.2, U26.24, U26.25
unnamed: C215.1, U26.36
unnamed: C215.2, U26.38
unnamed: C217.2, U26.26
unnamed: C218.2, U26.27
unnamed: C230.2, U29.19, U29.20
unnamed: C231.2, U29.24, U29.25
unnamed: C233.1, U29.36
unnamed: C233.2, U29.38
unnamed: C235.2, U29.26
unnamed: C236.2, U29.27
unnamed: C248.2, U32.19, U32.20
unnamed: C249.2, U32.24, U32.25
unnamed: C251.1, U32.36
unnamed: C251.2, U32.38
unnamed: C253.2, U32.26
unnamed: C254.2, U32.27
unnamed: C270.1, FB13.2
unnamed: C271.2, FB14.1
unnamed: C272.1, FB17.2
unnamed: C273.2, FB18.1
unnamed: C274.1, FB21.2
unnamed: C275.2, FB22.1
unnamed: C276.1, FB25.2
unnamed: C277.2, FB26.1
unnamed: C278.1, FB29.2
unnamed: C279.2, FB30.1
unnamed: C280.1, FB33.2
unnamed: C281.2, FB34.1
unnamed: C282.1, FB37.2
unnamed: C283.2, FB38.1
unnamed: C284.1, FB41.2
unnamed: C285.2, FB42.1
unnamed: C305.1, U42.20
unnamed: C308.1, U42.22
unnamed: C309.1, J15.7
unnamed: C309.2, R76.1, R80.2
unnamed: C310.1, J15.8
unnamed: C310.2, R77.1, R78.2
unnamed: C311.1, J15.3, R82.1
unnamed: D2.1, FB12.1, J3.6
unnamed: D3.1, FB13.1, J3.8
unnamed: D7.1, FB14.2, J3.7
unnamed: D8.1, FB15.2, J3.5
unnamed: D12.1, FB16.1, J4.6
unnamed: D13.1, FB17.1, J4.8
unnamed: D17.1, FB18.2, J4.7
unnamed: D18.1, FB19.2, J4.5
unnamed: D22.1, FB20.1, J5.6
unnamed: D23.1, FB21.1, J5.8
unnamed: D27.1, FB22.2, J5.7
unnamed: D28.1, FB23.2, J5.5
unnamed: D32.1, FB24.1, J6.6
unnamed: D33.1, FB25.1, J6.8
unnamed: D37.1, FB26.2, J6.7
unnamed: D38.1, FB27.2, J6.5
unnamed: D42.1, FB28.1, J7.6
unnamed: D43.1, FB29.1, J7.8
unnamed: D47.1, FB30.2, J7.7
unnamed: D48.1, FB31.2, J7.5
unnamed: D52.1, FB32.1, J8.6
unnamed: D53.1, FB33.1, J8.8
unnamed: D57.1, FB34.2, J8.7
unnamed: D58.1, FB35.2, J8.5
unnamed: D62.1, FB36.1, J9.6
unnamed: D63.1, FB37.1, J9.8
unnamed: D67.1, FB38.2, J9.7
unnamed: D68.1, FB39.2, J9.5
unnamed: D72.1, FB40.1, J10.6
unnamed: D73.1, FB41.1, J10.8
unnamed: D77.1, FB42.2, J10.7
unnamed: D78.1, FB43.2, J10.5
unnamed: D81.1, R83.1
unnamed: D82.1, R84.1
unnamed: D83.1, R85.1
unnamed: J1.1, SW1.1
unnamed: J15.1, R75.1, R81.1
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

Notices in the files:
parts and their libraries:
Copyright 2016 Accelerated Designs. All rights reserved.
